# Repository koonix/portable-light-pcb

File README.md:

# Portable Light

This circuit is used in a battery-powered portable handy light source,
consisting of an array of LEDs, powered by a Panasonic lithium battery.

## Modules

This circuit can be divided into these modules:

* [Control](#control-module)
* [Buck Converter](#buck-converter-module)
* [Charge Pump](#charge-pump-module)
* [Battery Charger](#battery-charger-module)

### Control Module

This module consists of the following:

* Microcontroller and it's driving components
* Shift register chip for driving the 7-Segment
* A 7-Segment and it's accompanying components

### Buck Converter Module

This module steps down the battery's voltage down to 3 Volts which is suitable
for the LEDs.

If battery voltage drops below 3 Volts however, this module is
turned off and the battery's voltage is directly passed through to the LEDs.

The signals required for control of the buck converter are provided by
the microcontroller.

### Charge Pump Module

The Control and Buck Converter modules require voltages upwards of 5 Volts
for their function, mainly needed by MOSFET's gates or the microcontroller
(When operating near 20MHz).

For that reason, this module consists of a 'Dickson charge pump' that converts
the 2.5v ~ 4.2v of the battery to 8v ~ 15v.

The signals required for driving the charge pump are provided by
the microcontroller.

### Battery Charger Module

Consisting of a LTC1733 Single-Cell Lithium Charge Controller, this module
takes care of topping off the battery when a charger is connected.

## More Detail

### How the 7-Segment is controlled/driven

A single CD4094 Shift-and-Store Register chip (similar to the infamous 595
Shift Register), Takes CLOCK, DATA, STROBE and OUTPUT-ENABLE signals from
the microcontroller and outputs the signals needed for controlling
the 7-Segment.

These signals are connected to bases of 7 PNP Transistors which drive the
LEDs of the 7-Segment directly.

### Control Module's input power

Taking advantage of two schottky diodes, power to the control
module will get sourced from either the battery or the charge pump (Which is
regulated down to 5 Volts.).

Because of the redundant-psu style dual-diode circuit, current will get sourced
from whichever source providing a higher voltage.

The diode accross Vout and Vin of the regulator is there to protect
the regulator if the Vout of the regulator goes higher than the Vin.
This shouldn't be much of a problem because of relatively small leakage
current of the dual-diode circuit, but is put there *'Just-in-Case™'*.

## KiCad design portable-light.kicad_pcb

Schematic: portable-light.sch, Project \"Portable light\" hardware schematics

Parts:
BT1: Battery_Cell; PinHeader_1x02_P2.54mm_Vertical
C1: 330n; C_1206_3216Metric_Pad1.42x1.75mm_HandSolder
J1: LOAD; PinHeader_1x02_P2.54mm_Vertical
J2: conn_sense_pump_2; Ribbon_2
J3: conn_sense_buck_2; Ribbon_2
J4: conn_batt_2; PinHeader_1x02_P2.54mm_Vertical
J5: conn_batt_1; PinHeader_1x02_P2.54mm_Vertical
J6: conn_sense_pump_1; Ribbon_2
J7: conn_sense_buck_1; Ribbon_2
J8: interboard-interface_2; Ribbon_8
J9: interboard-interface_1; Ribbon_8
NT1: Net-Tie_3_Tee; NetTie-3_SMD_Pad0.5mm
R1: 1R60; R_0805_2012Metric_Pad1.15x1.40mm_HandSolder

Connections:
+BATT-1: J5.2; also elsewhere on the board
+BATT-2: BT1.1 (+), C1.1, J4.2; also elsewhere on the board
+PUMP-1: J9.5; also elsewhere on the board
+PUMP-2: J8.5; also elsewhere on the board
/Buck converter/vout: J1.2 (A); also elsewhere on the board
/buck_high_mos_high_bjt_1: J9.4; also elsewhere on the board
/buck_high_mos_high_bjt_2: J8.4; also elsewhere on the board
/buck_high_mos_low_bjt_1: J9.3; also elsewhere on the board
/buck_high_mos_low_bjt_2: J8.3; also elsewhere on the board
/buck_low_mos_high_bjt_1: J9.2; also elsewhere on the board
/buck_low_mos_high_bjt_2: J8.1; also elsewhere on the board
/buck_low_mos_low_bjt_1: J9.1; also elsewhere on the board
/buck_low_mos_low_bjt_2: J8.2; also elsewhere on the board
/gnd_vsense_buck_1: J7.1; also elsewhere on the board
/gnd_vsense_pump_1: J6.1; also elsewhere on the board
/pump_clka_1: J9.8; also elsewhere on the board
/pump_clka_2: J8.7; also elsewhere on the board
/pump_clkb_1: J9.7; also elsewhere on the board
/pump_clkb_2: J8.8; also elsewhere on the board
/pump_onoff_1: J9.6; also elsewhere on the board
/pump_onoff_2: J8.6; also elsewhere on the board
/vsense_buck_1: J7.2; also elsewhere on the board
/vsense_buck_2: J3.2; also elsewhere on the board
/vsense_pump_1: J6.2; also elsewhere on the board
/vsense_pump_2: J2.2; also elsewhere on the board
GND: NT1.3; also elsewhere on the board
GND-CHARGER: BT1.2 (-), J4.1, NT1.1, R1.2; also elsewhere on the board
GNDA: J2.1, J3.1, NT1.2; also elsewhere on the board
GNDPWR: J1.1 (K), J5.1; also elsewhere on the board
unnamed: C1.2, R1.1

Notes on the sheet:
Power

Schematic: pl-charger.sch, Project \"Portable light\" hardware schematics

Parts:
C2, C3: 100n; C_1206_3216Metric_Pad1.42x1.75mm_HandSolder
C4: 10u; C_Radial_D5.0mm_H7.0mm_P2.00mm
J10: Charger; PinHeader_1x02_P2.54mm_Vertical
Q1: Q_PNP_BCE; SOT-23
Q2: MMBT2222A; SOT-23
R2, R3, R6, R8, R9, R11: 1K; R_0603_1608Metric_Pad1.05x0.95mm_HandSolder
R4: 150K; R_0603_1608Metric_Pad1.05x0.95mm_HandSolder
R5: 270K; R_0603_1608Metric_Pad1.05x0.95mm_HandSolder
R7: 10K; R_0603_1608Metric_Pad1.05x0.95mm_HandSolder
R10: 10K; R_1206_3216Metric_Pad1.42x1.75mm_HandSolder
R12: 510R; R_0805_2012Metric_Pad1.15x1.40mm_HandSolder
U1: LTC1733EMSEPBF; MSOP-10_MSE

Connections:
+5V: R4.1; also elsewhere on the board
+BATT-2: Q1.2 (C), U1.9 (BAT); also elsewhere on the board
+CHARGER: C4.1, J10.1, U1.2 (VCC), U1.8 (SEL)
/Charger/acpr_out: R11.2; also elsewhere on the board
/Controller/charger_chrg_in: R3.2, R5.2, U1.1 (*CHRG); also elsewhere on the board
/Controller/charger_chrg_pulldown_or_float_out: R2.1; also elsewhere on the board
/Controller/charger_fault_in: R6.1; also elsewhere on the board
/Controller/charger_prog_disable_charging: R10.1; also elsewhere on the board
/Controller/charger_prog_enable_charging: R7.2; also elsewhere on the board
GND-CHARGER: C2.2, C3.2, C4.2, J10.2, Q2.2 (E), U1.5 (GND), U1.6 (NTC), U1.11 (EPAD); also elsewhere on the board
unnamed: C2.1, C3.1, U1.4 (TIMER)
unnamed: Q1.1 (B), R7.1
unnamed: Q1.3 (E), R8.1
unnamed: Q2.1 (B), R10.2
unnamed: Q2.3 (C), R12.2
unnamed: R2.2, R3.1
unnamed: R4.2, R5.1
unnamed: R6.2, U1.3 (*FAULT)
unnamed: R8.2, R9.1, U1.7 (PROG)
unnamed: R11.1, U1.10 (*ACPR)
unnamed: R9.2, R12.1

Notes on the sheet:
Charge controller

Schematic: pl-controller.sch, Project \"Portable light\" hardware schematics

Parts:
C5, C6: 15n; C_1206_3216Metric_Pad1.42x1.75mm_HandSolder
C7, C8: 22p; C_1206_3216Metric_Pad1.42x1.75mm_HandSolder
C9, C11, C12, C14, C15: 100n; C_1206_3216Metric_Pad1.42x1.75mm_HandSolder
C10, C13: 300n; C_0805_2012Metric_Pad1.15x1.40mm_HandSolder
D1: M7; D_SMA_Handsoldering
D2, D3: 1N5819; D_SMA_Handsoldering
J11: Conn_01x05; PinHeader_1x05_P2.54mm_Vertical
J12: Conn_01x08; Ribbon_8
J13: Conn_01x02-Connector_Generic; Ribbon_2
Q3: Q_NMOS_DGS; SOT-23
Q4, Q5, Q6, Q7, Q8, Q9, Q10: Q_PNP_BCE; SOT-23
R13: 10K; R_1206_3216Metric_Pad1.42x1.75mm_HandSolder
R14: 1K; R_0603_1608Metric_Pad1.05x0.95mm_HandSolder
R15, R16, R17, R18, R19, R20, R21: 475R; R_1206_3216Metric_Pad1.42x1.75mm_HandSolder
R22, R23, R24, R25, R26, R27, R28: 5K1; C_0805_2012Metric_Pad1.15x1.40mm_HandSolder
U2: ATmega88PA-AU; TQFP-32_7x7mm_P0.8mm
U3: CD4094BPW; SOP-16
U4: L78L05_SOT89; SOT-89-3
Y1: 20MHz Crystal; Crystal_SMD_HC49-SD

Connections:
+5V: C10.2, C11.2, C12.2, D2.1 (K), D3.1 (K), Q4.2 (C), Q5.2 (C), Q6.2 (C), Q7.2 (C), Q8.2 (C), Q9.2 (C), Q10.2 (C), U2.4 (VCC), U2.6 (VCC), U2.18 (AVCC), U3.16 (VDD); also elsewhere on the board
+BATT-2: D3.2 (A); also elsewhere on the board
+PUMP-2: C14.1, D1.1 (K), U4.3 (IN); also elsewhere on the board
/Charger/acpr_out: U2.25 (PC2); also elsewhere on the board
/Controller/button: C13.2, J13.1, R14.2
/Controller/charger_chrg_in: U2.23 (PC0); also elsewhere on the board
/Controller/charger_chrg_pulldown_or_float_out: U2.26 (PC3); also elsewhere on the board
/Controller/charger_fault_in: U2.24 (PC1); also elsewhere on the board
/Controller/charger_prog_disable_charging: U2.28 (PC5); also elsewhere on the board
/Controller/charger_prog_enable_charging: U2.27 (PC4); also elsewhere on the board
/Controller/miso: J11.4, R14.1, U2.16 (PB4)
/Controller/reset: J11.2, U2.29 (~RESET~/PC6)
/Controller/sck: J11.3, U2.17 (PB5)
/Controller/seg-1: Q4.3 (E), R15.2
/Controller/seg-2: Q5.3 (E), R16.2
/Controller/seg-3: Q6.3 (E), R17.2
/Controller/seg-4: Q8.3 (E), R18.2
/Controller/seg-5: Q10.3 (E), R19.2
/Controller/seg-6: Q9.3 (E), R20.2
/Controller/seg-7: Q7.3 (E), R21.2
/Controller/seg-base-1: R26.2, U3.4 (Q1)
/Controller/seg-base-2: R24.2, U3.5 (Q2)
/Controller/seg-base-3: R23.2, U3.6 (Q3)
/Controller/seg-base-4: R22.2, U3.7 (Q4)
/Controller/seg-base-5: R28.2, U3.14 (Q5)
/Controller/seg-base-6: R27.2, U3.13 (Q6)
/Controller/seg-base-7: R25.2, U3.12 (Q7)
/Controller/shiftregister-clock: U2.30 (PD0), U3.3 (CLOCK)
/Controller/shiftregister-data: U2.31 (PD1), U3.2 (DATA)
/Controller/shiftregister-enable: U2.2 (PD4), U3.15 (OUTPUT_ENABLE)
/Controller/shiftregister-strobe: U2.32 (PD2), U3.1 (STROBE)
/Controller/shiftregister-vss: R13.2, U2.11 (PD7)
/Controller/xtal1: C7.2, U2.7 (XTAL1/PB6), Y1.1
/Controller/xtal2: C8.2, U2.8 (XTAL2/PB7), Y1.2
/buck_high_mos_high_bjt_2: U2.1 (PD3); also elsewhere on the board
/buck_high_mos_low_bjt_2: J11.5, U2.15 (PB3); also elsewhere on the board
/buck_low_mos_high_bjt_2: U2.9 (PD5); also elsewhere on the board
/buck_low_mos_low_bjt_2: U2.10 (PD6); also elsewhere on the board
/pump_clka_2: U2.13 (PB1); also elsewhere on the board
/pump_clkb_2: U2.14 (PB2); also elsewhere on the board
/pump_onoff_2: U2.12 (PB0); also elsewhere on the board
/vsense_buck_2: C6.2, U2.22 (ADC7); also elsewhere on the board
/vsense_pump_2: C5.2, U2.19 (ADC6); also elsewhere on the board
GND: C7.1, C8.1, C10.1, C11.1, C13.1, C14.2, C15.2, J11.1, J12.8, J13.2, Q3.3 (S), U2.3 (GND), U2.5 (GND), U2.21 (GND), U4.2 (GND); also elsewhere on the board
GNDA: C5.1, C6.1, C9.2, C12.1; also elsewhere on the board
unnamed: C9.1, U2.20 (AREF)
unnamed: C15.1, D1.2 (A), D2.2 (A), U4.1 (OUT)
unnamed: J12.1, R15.1
unnamed: J12.2, R16.1
unnamed: J12.3, R17.1
unnamed: J12.4, R18.1
unnamed: J12.5, R19.1
unnamed: J12.6, R20.1
unnamed: J12.7, R21.1
unnamed: Q3.1 (D), U3.8 (VSS)
unnamed: Q3.2 (G), R13.1
unnamed: Q4.1 (B), R22.1
unnamed: Q5.1 (B), R23.1
unnamed: Q6.1 (B), R24.1
unnamed: Q7.1 (B), R25.1
unnamed: Q8.1 (B), R26.1
unnamed: Q9.1 (B), R27.1
unnamed: Q10.1 (B), R28.1

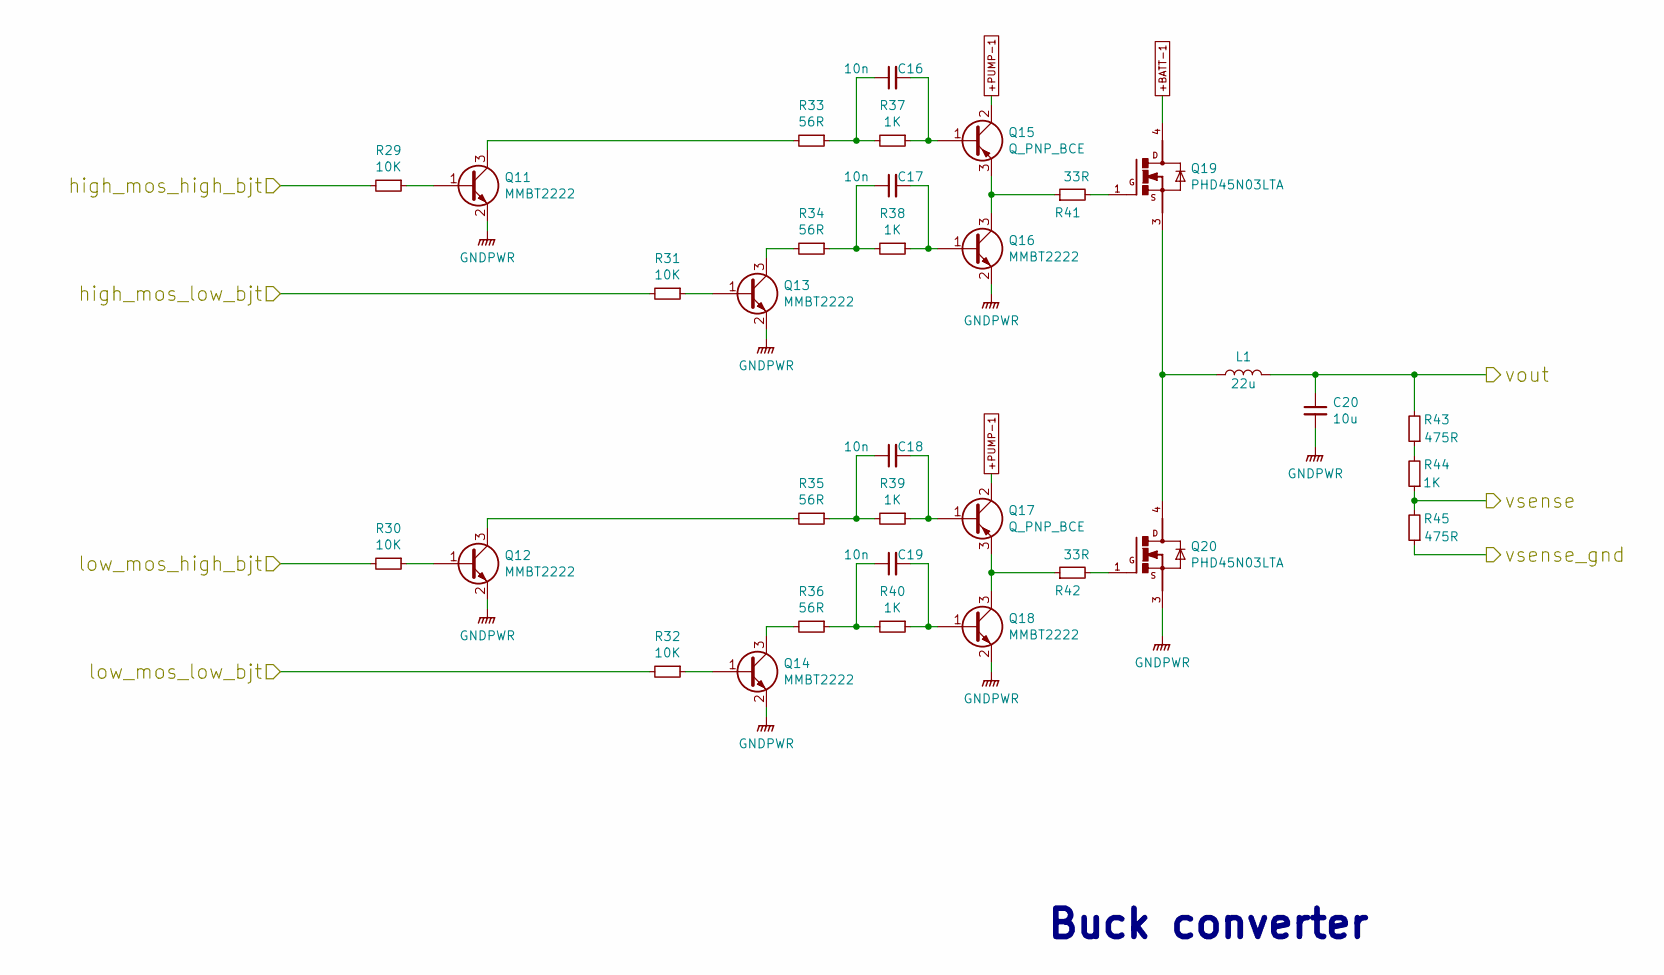
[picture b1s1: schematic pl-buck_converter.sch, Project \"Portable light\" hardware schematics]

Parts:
C16, C17, C18, C19: 10n; C_0805_2012Metric_Pad1.15x1.40mm_HandSolder
C20: 10u; C_Radial_D5.0mm_H7.0mm_P2.00mm
L1: 22u; CP_Radial_D8.0mm_P5.00mm
Q11, Q12, Q13, Q14, Q16, Q18: MMBT2222; SOT-23
Q15, Q17: Q_PNP_BCE; SOT-23
Q19, Q20: PHD45N03LTA; DPAK
R29, R30, R31, R32: 10K; R_0805_2012Metric_Pad1.15x1.40mm_HandSolder
R33, R34, R35, R36: 56R; R_0805_2012Metric_Pad1.15x1.40mm_HandSolder
R37, R38, R39, R40, R44: 1K; R_0603_1608Metric_Pad1.05x0.95mm_HandSolder
R41, R42: 33R; R_0805_2012Metric_Pad1.15x1.40mm_HandSolder
R43: 475R; R_1206_3216Metric_Pad1.42x1.75mm_HandSolder
R45: 475R; R_0805_2012Metric_Pad1.15x1.40mm_HandSolder

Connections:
+BATT-1: Q19.4; also elsewhere on the board
+PUMP-1: Q15.2 (C), Q17.2 (C); also elsewhere on the board
/Buck converter/vout: C20.1, L1.2, R43.2; also elsewhere on the board
/buck_high_mos_high_bjt_1: R29.2; also elsewhere on the board
/buck_high_mos_low_bjt_1: R31.2; also elsewhere on the board
/buck_low_mos_high_bjt_1: R30.2; also elsewhere on the board
/buck_low_mos_low_bjt_1: R32.2; also elsewhere on the board
/gnd_vsense_buck_1: R45.1; also elsewhere on the board
/vsense_buck_1: R44.1, R45.2; also elsewhere on the board
GNDPWR: C20.2, Q11.2 (E), Q12.2 (E), Q13.2 (E), Q14.2 (E), Q16.2 (E), Q18.2 (E), Q20.3; also elsewhere on the board
unnamed: C16.1, R33.1, R37.2
unnamed: C16.2, Q15.1 (B), R37.1
unnamed: C17.1, R34.1, R38.2
unnamed: C17.2, Q16.1 (B), R38.1
unnamed: C18.1, R35.1, R39.2
unnamed: C18.2, Q17.1 (B), R39.1
unnamed: C19.1, R36.1, R40.2
unnamed: C19.2, Q18.1 (B), R40.1
unnamed: L1.1, Q19.3, Q20.4
unnamed: Q11.1 (B), R29.1
unnamed: Q11.3 (C), R33.2
unnamed: Q12.1 (B), R30.1
unnamed: Q12.3 (C), R35.2
unnamed: Q13.1 (B), R31.1
unnamed: Q13.3 (C), R34.2
unnamed: Q14.1 (B), R32.1
unnamed: Q14.3 (C), R36.2
unnamed: Q15.3 (E), Q16.3 (C), R41.1
unnamed: Q17.3 (E), Q18.3 (C), R42.1
unnamed: Q19.1, R41.2
unnamed: Q20.1, R42.2
unnamed: R43.1, R44.2

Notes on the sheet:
Buck converter

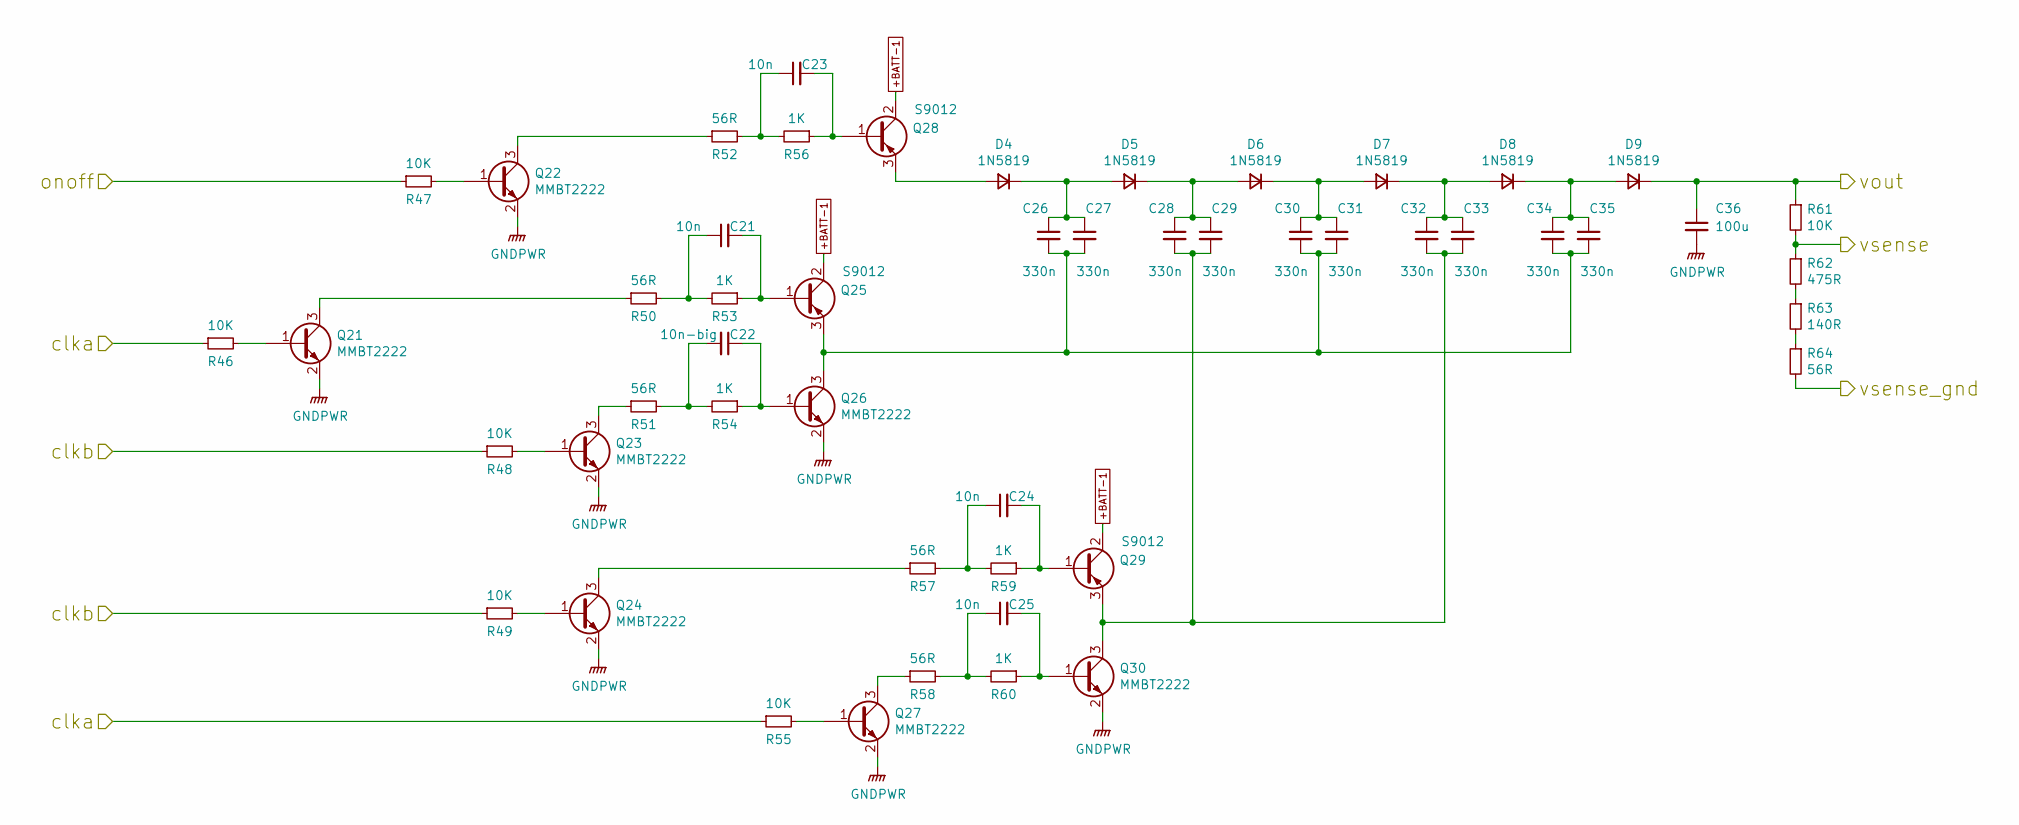
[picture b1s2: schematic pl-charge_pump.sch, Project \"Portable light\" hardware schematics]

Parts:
C21, C23, C24, C25: 10n; C_0805_2012Metric_Pad1.15x1.40mm_HandSolder
C22: 10n-big; C_1206_3216Metric_Pad1.42x1.75mm_HandSolder
C26, C27, C28, C29, C30, C31, C32, C33, C34, C35: 330n; C_1206_3216Metric_Pad1.42x1.75mm_HandSolder
C36: 100u; CP_Elec_6.3x5.9
D4, D5, D6, D7, D8, D9: 1N5819; D_SMA_Handsoldering
Q21, Q22, Q23, Q24, Q26, Q27, Q30: MMBT2222; SOT-23
Q25, Q28, Q29: S9012; SOT-23
R46, R47, R48, R49, R55, R61: 10K; C_0805_2012Metric_Pad1.15x1.40mm_HandSolder
R50, R51, R52, R57, R58, R64: 56R; C_0805_2012Metric_Pad1.15x1.40mm_HandSolder
R53, R54, R56, R59, R60: 1K; R_0603_1608Metric_Pad1.05x0.95mm_HandSolder
R62: 475R; C_1206_3216Metric_Pad1.42x1.75mm_HandSolder
R63: 140R; C_1206_3216Metric_Pad1.42x1.75mm_HandSolder

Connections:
+BATT-1: Q25.2 (C), Q28.2 (C), Q29.2 (C); also elsewhere on the board
+PUMP-1: C36.1, D9.1 (K), R61.1; also elsewhere on the board
/gnd_vsense_pump_1: R64.2; also elsewhere on the board
/pump_clka_1: R46.1, R55.1; also elsewhere on the board
/pump_clkb_1: R48.1, R49.1; also elsewhere on the board
/pump_onoff_1: R47.1; also elsewhere on the board
/vsense_pump_1: R61.2, R62.1; also elsewhere on the board
GNDPWR: C36.2, Q21.2 (E), Q22.2 (E), Q23.2 (E), Q24.2 (E), Q26.2 (E), Q27.2 (E), Q30.2 (E); also elsewhere on the board
unnamed: C21.1, R50.2, R53.2
unnamed: C21.2, Q25.1 (B), R53.1
unnamed: C22.1, Q26.1 (B), R54.1
unnamed: C22.2, R51.2, R54.2
unnamed: C23.1, R52.2, R56.2
unnamed: C23.2, Q28.1 (B), R56.1
unnamed: C24.1, R57.2, R59.2
unnamed: C24.2, Q29.1 (B), R59.1
unnamed: C25.1, R58.2, R60.2
unnamed: C25.2, Q30.1 (B), R60.1
unnamed: C26.1, C27.1, D4.1 (K), D5.2 (A)
unnamed: C26.2, C27.2, C30.2, C31.2, C34.2, C35.2, Q25.3 (E), Q26.3 (C)
unnamed: C28.1, C29.1, D5.1 (K), D6.2 (A)
unnamed: C28.2, C29.2, C32.2, C33.2, Q29.3 (E), Q30.3 (C)
unnamed: C30.1, C31.1, D6.1 (K), D7.2 (A)
unnamed: C32.1, C33.1, D7.1 (K), D8.2 (A)
unnamed: C34.1, C35.1, D8.1 (K), D9.2 (A)
unnamed: D4.2 (A), Q28.3 (E)
unnamed: Q21.1 (B), R46.2
unnamed: Q21.3 (C), R50.1
unnamed: Q22.1 (B), R47.2
unnamed: Q22.3 (C), R52.1
unnamed: Q23.1 (B), R48.2
unnamed: Q23.3 (C), R51.1
unnamed: Q24.1 (B), R49.2
unnamed: Q24.3 (C), R57.1
unnamed: Q27.1 (B), R55.2
unnamed: Q27.3 (C), R58.1
unnamed: R62.2, R63.1
unnamed: R63.2, R64.1

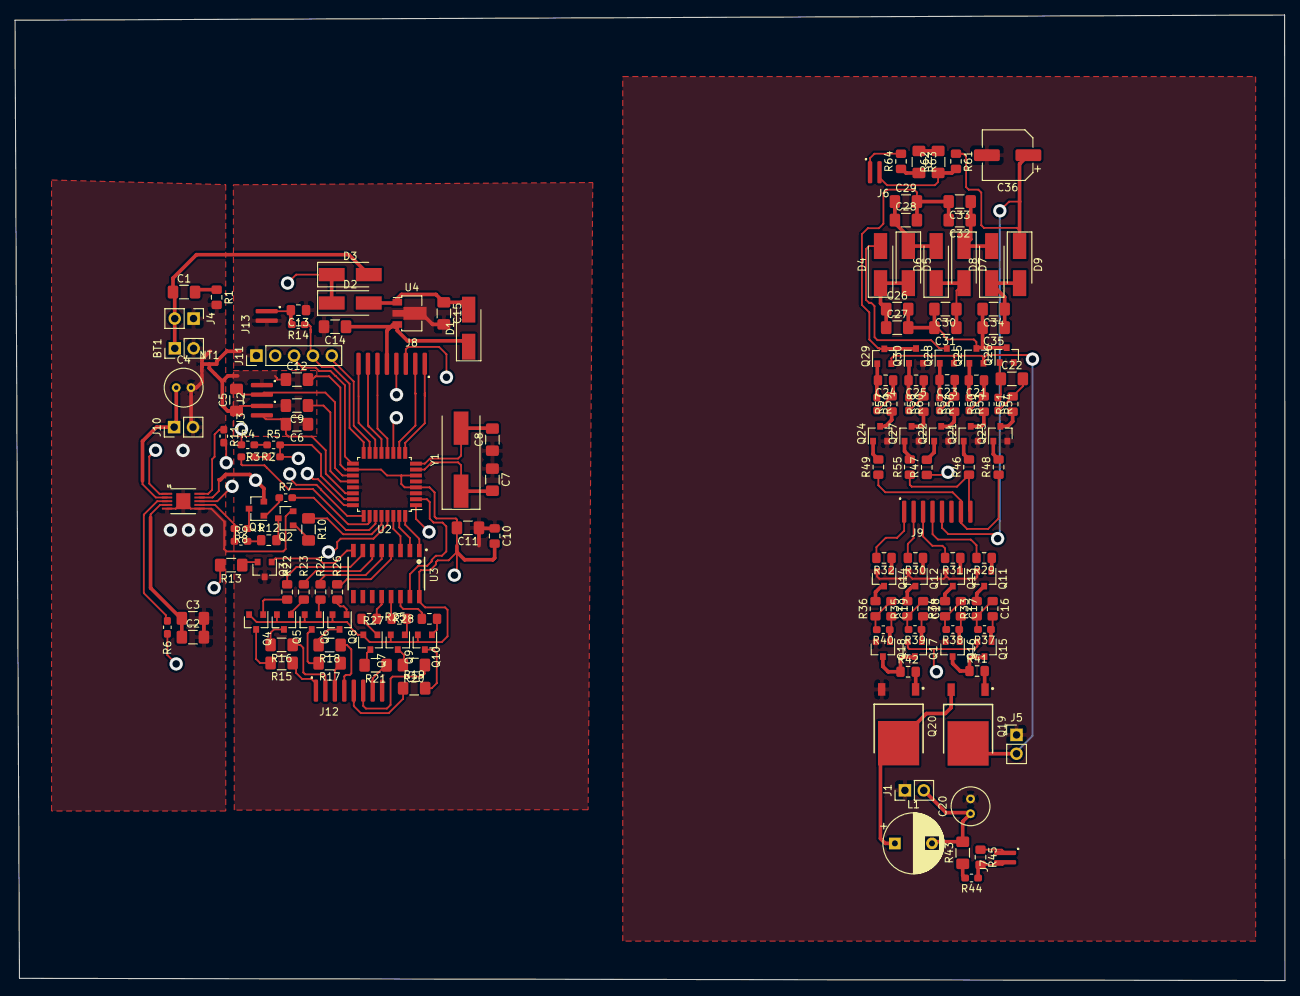
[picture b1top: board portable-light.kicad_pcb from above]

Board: 10 copper layers, 171.2 x 130.2 mm, 160 parts (0 on the bottom side), 144 nets.

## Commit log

2020-07-23 Schematics and PCB layout complete
2020-07-24 commit before checkout
2020-07-24 LTC1733 bug fixed
2020-07-24 AVR Charge-pump bug fixed
2020-07-25 Added push-button
2020-07-25 First review and refactoring complete; PCB is ready
2020-08-10 divided schematics into multiple sheets moved to arch
2020-08-29 Fixed hierarchical sheet for microcontroller unit
2020-08-29 Removed *-bak files
2020-08-29 Charger hierarchical sheet fixed
2020-09-06 Schematic's overall structure is finished
2020-09-06 KiKac Cache file removed from repo, minor changes of README.md
2020-09-12 Removed 'rescue' files
2020-09-12 Added component values
2020-09-25 Schematics redesigned and fixed
2020-09-25 Updated pcb from schem
2020-09-27 Cleaned up the PCB a little bit, Fixed some errors in schematics
2020-09-27 Fixed some minor stuff in schematics, Refined the PCB a little bit more
2020-10-02 Seperated the two PCBs successfully, All DRC errors fixed, gotta double check the circuit
2020-11-24 Added the 3d model image
2020-11-24 Added 3d model image to README
2020-11-24 Fixed the image thingy in README
2020-11-24 Fixed the plot directory
